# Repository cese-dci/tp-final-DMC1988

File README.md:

## Trabajo práctico final de la asignatura DCI ##
Este repositorio contiene el trabajo práctico final para la asignatura de Diseño de Circuitos Impresos de la carrera de posgrado de FIUBA.

* Autor: Damián Caputo
* Título corto del trabajo:  Replica driver puente H L298
* Descripción:  Diseño de esquemático y PCB del modulo puente H L298.

## Licencia de este trabajo ##
Diseño bajo licencia CERN-OHL-P.

## Estructura del TP FINAL ##

Se propone y se pide utilizar la siguiente estructura.

* doc: Toda la información sobre el circuito, principalmente de autoría o procesamiento propio. Por ejemplo:
  * Notas de ingeniería propias.
  * Notas de aplicación propias.
  * Estudios previos, estado del arte, resumen de las investigaciones.
  * Notas con cálculos.
  * Dibujos adicionales.
  * Fotos de los prototipos.
  * Presupuestos, cotizaciones.
* info: Toda la iformación recolectada, principalmente de terceros, como por ejemplo:
  * Hojas de datos.
  * Notas de aplicación.
  * Info de productos comerciales.
  * Info en internet.
* pcb: Archivos de diseño esquemático y pcb.

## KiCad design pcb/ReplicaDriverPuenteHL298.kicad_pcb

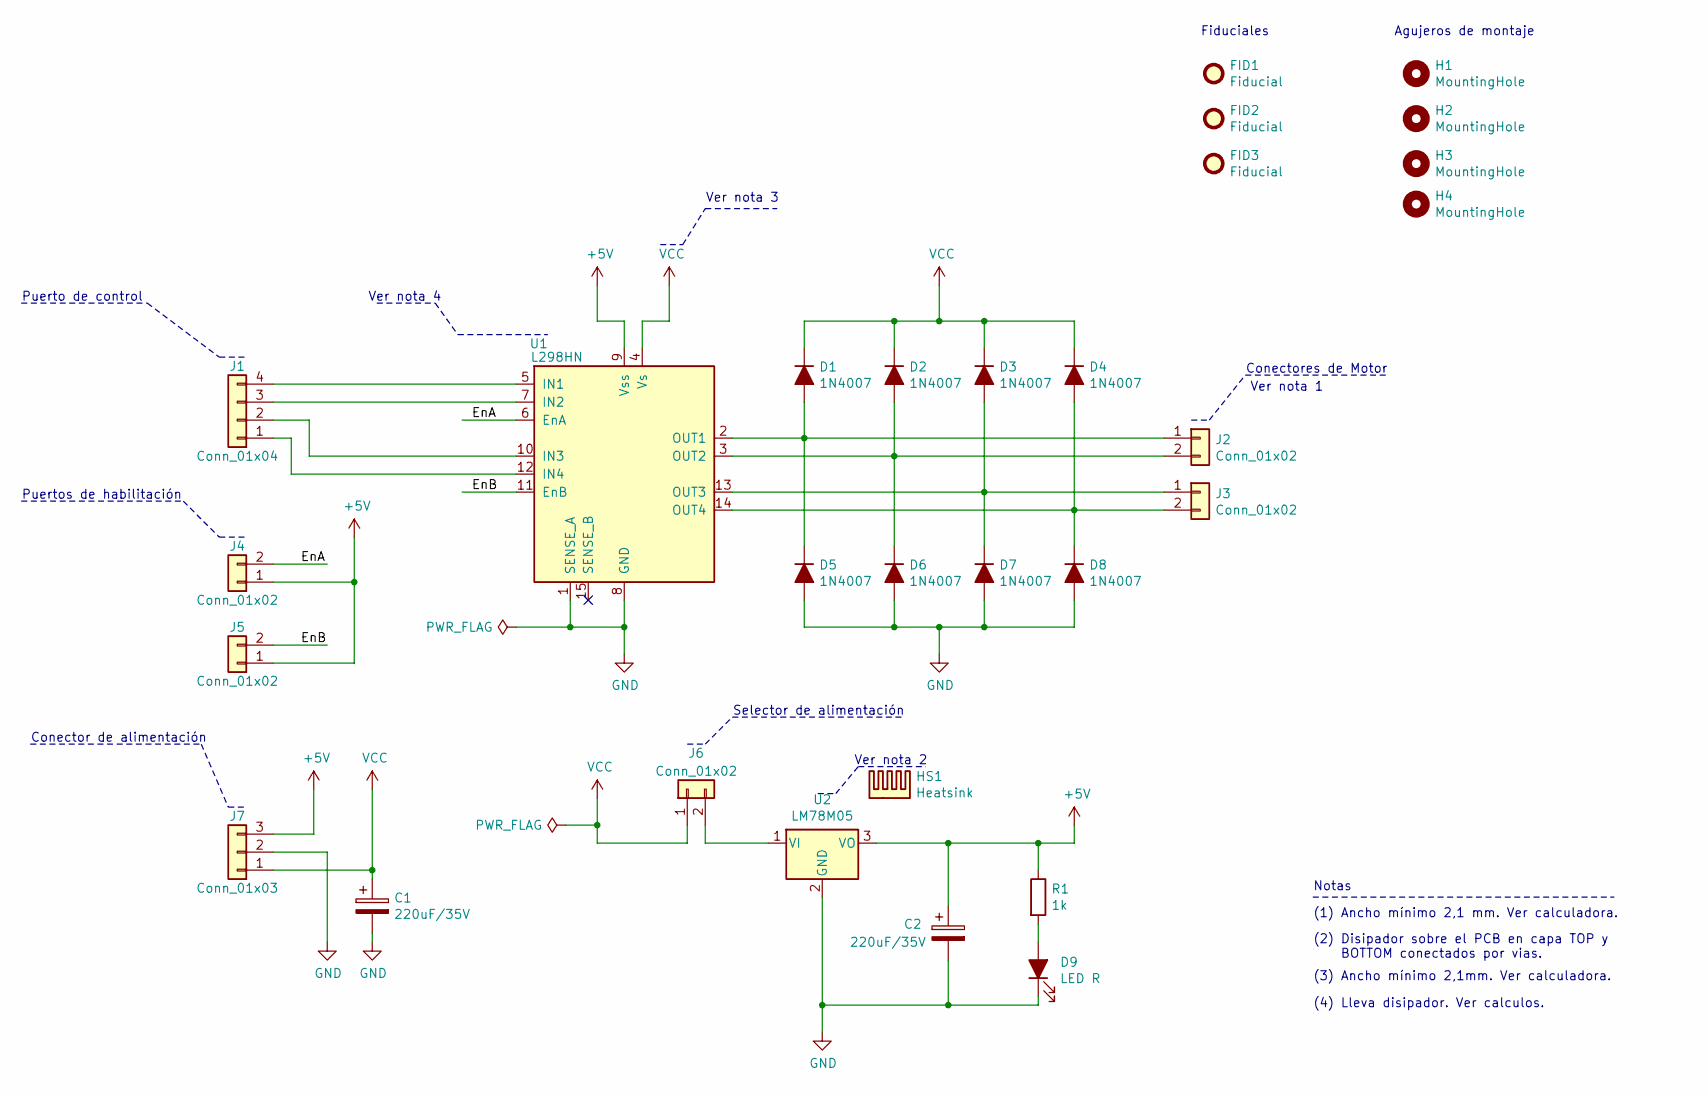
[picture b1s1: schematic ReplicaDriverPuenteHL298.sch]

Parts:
C1, C2: 220uF/35V; CP_Elec_6.3x5.8
D1, D2, D3, D4, D5, D6, D7, D8: 1N4007; D_SMA
D9: LED R; LED_0805_HandSoldering
FID1, FID2, FID3: Fiducial; Fiducial_0.5mm_Dia_1mm_Outer
H1, H2, H3, H4: MountingHole; MountingHole_2.2mm_M2
HS1: Heatsink
J1: Conn_01x04; Pin_Header_Straight_1x04_Pitch2.54mm
J2, J3: Conn_01x02; TerminalBlock_bornier-2_P5.08mm
J4, J5, J6: Conn_01x02; Pin_Header_Straight_1x02_Pitch2.54mm
J7: Conn_01x03; TerminalBlock_bornier-3_P5.08mm
R1: 1k; R_0805_HandSoldering
U1: L298HN; TO127P2020X500X2100-15
U2: LM78M05; TO-252-2

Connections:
+5V: C2.1, J4.1, J5.1, J7.3, R1.1, U1.9 (Vss), U2.3 (VO)
/EnA: J4.2, U1.6 (EnA)
/EnB: J5.2, U1.11 (EnB)
GND: C1.2, C2.2, D5.2 (A), D6.2 (A), D7.2 (A), D8.2 (A), D9.1 (K), J7.2, U1.1 (SENSE_A), U1.8 (GND), U2.2 (GND)
unnamed: D1.2 (A), D5.1 (K), J2.1, U1.2 (OUT1)
unnamed: D2.2 (A), D6.1 (K), J2.2, U1.3 (OUT2)
unnamed: D3.2 (A), D7.1 (K), J3.1, U1.13 (OUT3)
unnamed: D4.2 (A), D8.1 (K), J3.2, U1.14 (OUT4)
unnamed: D9.2 (A), R1.2
unnamed: J1.1, U1.12 (IN4)
unnamed: J1.2, U1.10 (IN3)
unnamed: J1.3, U1.7 (IN2)
unnamed: J1.4, U1.5 (IN1)
unnamed: J6.2, U2.1 (VI)
VCC: C1.1, D1.1 (K), D2.1 (K), D3.1 (K), D4.1 (K), J6.1, J7.1, U1.4 (Vs)

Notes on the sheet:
Conectores de Motor
Puertos de habilitación
Puerto de control
Conector de alimentación
Selector de alimentación
Ver nota 2
Agujeros de montaje
Ver nota 1
Ver nota 3
Notas
(1) Ancho mínimo 2,1 mm. Ver calculadora.
Ver nota 4
(2) Disipador sobre el PCB en capa TOP y BOTTOM conectados por vias.
(3) Ancho mínimo 2,1mm. Ver calculadora.
(4) Lleva disipador. Ver calculos.
Fiduciales

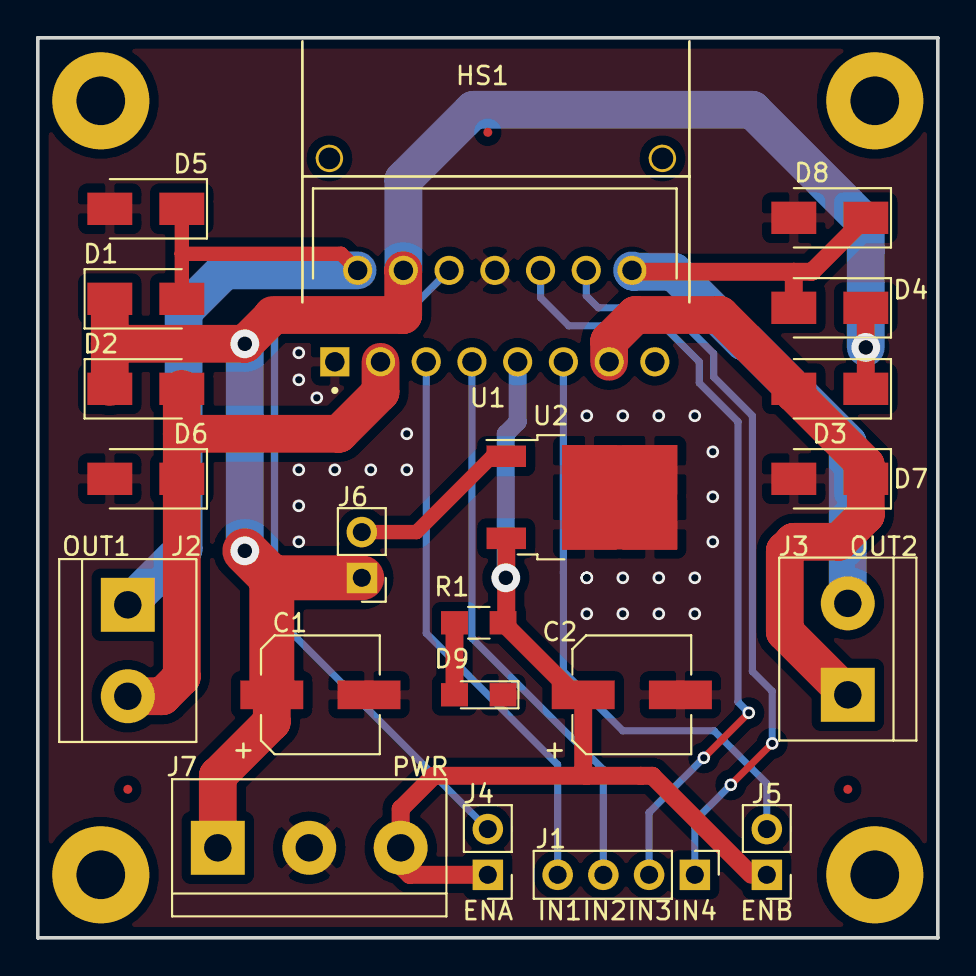
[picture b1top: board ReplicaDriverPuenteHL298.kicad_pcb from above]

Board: 2 copper layers, 50.0 x 50.0 mm, 29 parts (0 on the bottom side), 15 nets.
